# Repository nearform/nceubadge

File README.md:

# NodeConf EU 2017 Badge

### All documentation including the Getting Started Guide and explanations of the sample code in this repo is available on [nodeconfeubadge.org](http://nodeconfeubadge.org)

## Hardware
This is an Open Source Hardware project. Schematics and board design files are available in the /hardware directory

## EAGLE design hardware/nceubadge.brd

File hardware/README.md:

Nodeconf EU hardware design files
=================================

The Badge's hardware was designed in [Eagle CAD](https://www.autodesk.com/products/eagle/overview)

You'll find the original design files here, as well as PDF versions of the schematic and board.

Parts
-----

The main components are:

* [MDBT42Q](http://www.raytac.com/download/MDBT42/MDBT42Q%20&%20MDBT42Q-P-Version%20D.pdf) Bluetooth Module (with [nRF52832](https://www.nordicsemi.com/eng/Products/Bluetooth-low-energy/nRF52832) MCU)
* [MCCOG128064B12W-SPR](http://www.farnell.com/datasheets/2151561.pdf) LCD

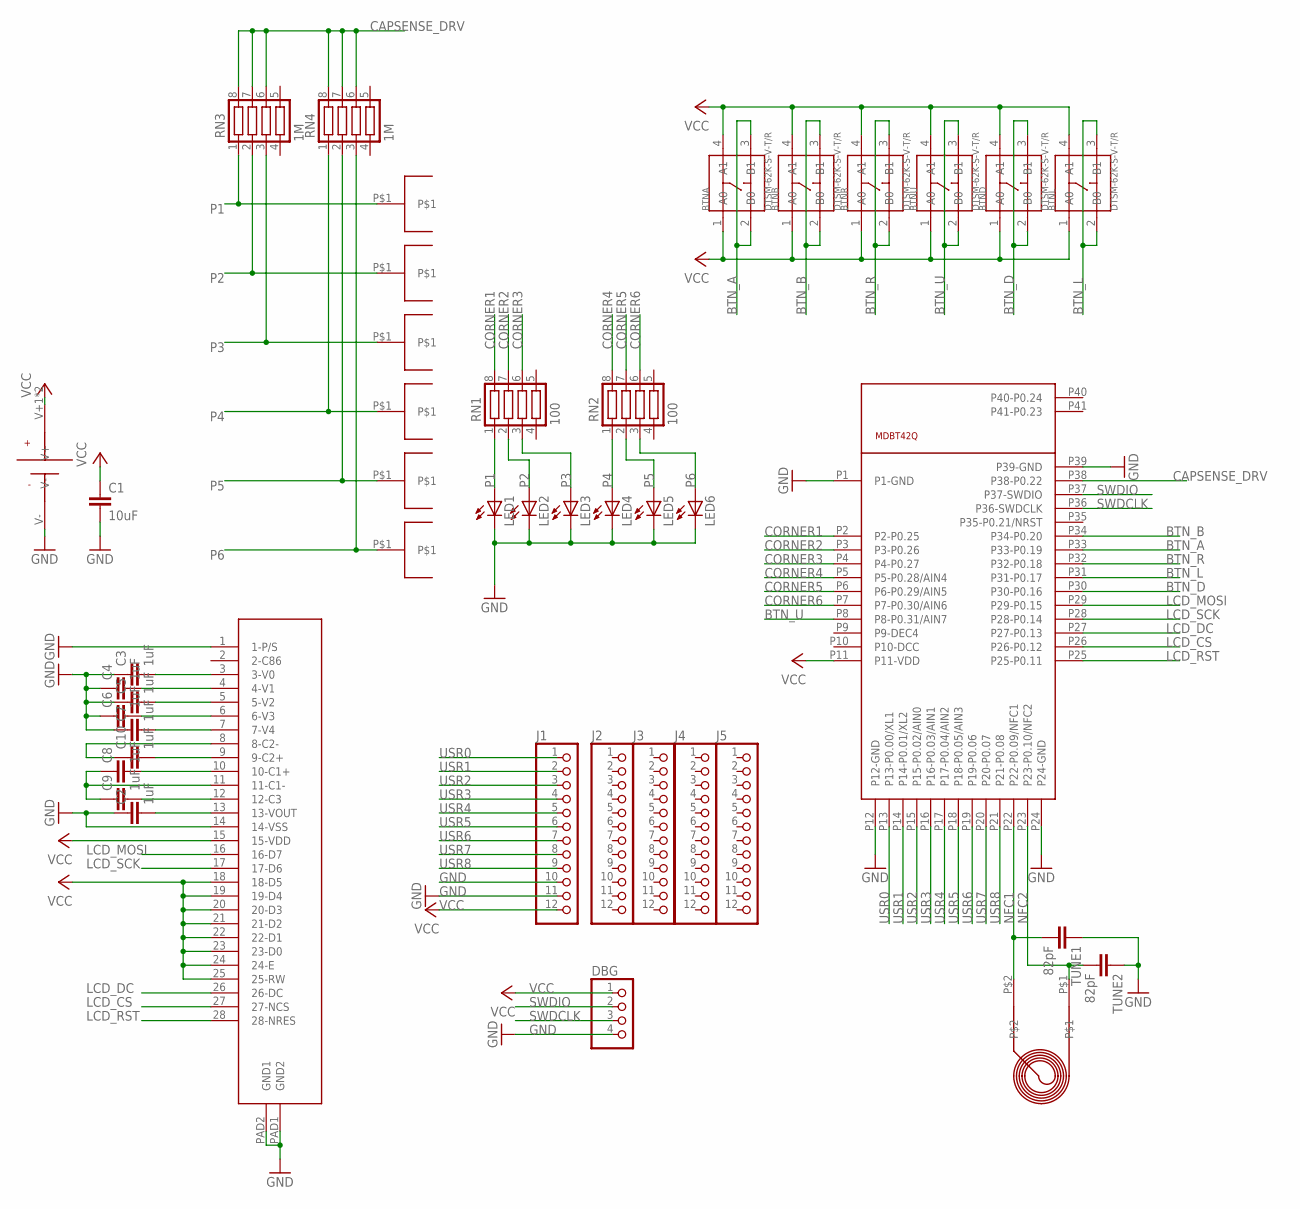
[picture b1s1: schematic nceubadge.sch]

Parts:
BTNA: DTSM-62K-S-V-T/R; SW4-SMD-6.0X6.0X5.0MM
BTNB: DTSM-62K-S-V-T/R; SW4-SMD-6.0X6.0X5.0MM
BTND: DTSM-62K-S-V-T/R; SW4-SMD-6.0X6.0X5.0MM
BTNL: DTSM-62K-S-V-T/R; SW4-SMD-6.0X6.0X5.0MM
BTNR: DTSM-62K-S-V-T/R; SW4-SMD-6.0X6.0X5.0MM
BTNU: DTSM-62K-S-V-T/R; SW4-SMD-6.0X6.0X5.0MM
C1: 10uF; C0805K
C2, C3, C4, C5, C6, C7, C8, C9, C10: 1uF; C0603
DBG: PINHD-1X4; 1X04
J1, J2, J3, J4, J5: PINHD-1X12_2.54-S; 1X12-S
J8: KEYSTONE-3003
LCD: MCCOG128064B12W; MCOG128064B12W-SPR
LED1, LED2, LED3, LED4, LED5, LED6: LED5MM
RN1, RN2: 100; CTS742C083
RN3, RN4: 1M; CTS742C083
TUNE1, TUNE2: 82pF; C0603
U1: MDBT42Q; MDBT40
U$2, U$3, U$4, U$5, U$6, U$7: BANANAPLUG
U$8: NFC

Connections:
BTN_A: BTNA.2 (B0), BTNA.3 (B1), U1.P33 (P33-P0.19)
BTN_B: BTNB.2 (B0), BTNB.3 (B1), U1.P34 (P34-P0.20)
BTN_D: BTND.2 (B0), BTND.3 (B1), U1.P30 (P30-P0.16)
BTN_L: BTNL.2 (B0), BTNL.3 (B1), U1.P31 (P31-P0.17)
BTN_R: BTNR.2 (B0), BTNR.3 (B1), U1.P32 (P32-P0.18)
BTN_U: BTNU.2 (B0), BTNU.3 (B1), U1.P8 (P8-P0.31/AIN7)
CAPSENSE_DRV: RN3.6, RN3.7, RN3.8, RN4.6, RN4.7, RN4.8, U1.P38 (P38-P0.22)
CORNER1: RN1.8, U1.P2 (P2-P0.25)
CORNER2: RN1.7, U1.P3 (P3-P0.26)
CORNER3: RN1.6, U1.P4 (P4-P0.27)
CORNER4: RN2.8, U1.P5 (P5-P0.28/AIN4)
CORNER5: RN2.7, U1.P6 (P6-P0.29/AIN5)
CORNER6: RN2.6, U1.P7 (P7-P0.30/AIN6)
GND: C1.2, C2.1, C3.1, C4.1, C5.1, C6.1, C7.1, DBG.4, J1.10, J1.11, J8.V-, LCD.1 (1-P/S), LCD.14 (14-VSS), LCD.PAD1 (GND2), LCD.PAD2 (GND1), LED1.K (C), LED2.K (C), LED3.K (C), LED4.K (C), LED5.K (C), LED6.K (C), TUNE1.1, TUNE2.1, U1.P1 (P1-GND), U1.P12 (P12-GND), U1.P24 (P24-GND), U1.P39 (P39-GND)
LCD_CS: LCD.27 (27-NCS), U1.P26 (P26-P0.12)
LCD_DC: LCD.26 (26-DC), U1.P27 (P27-P0.13)
LCD_MOSI: LCD.16 (16-D7), U1.P29 (P29-P0.15)
LCD_RST: LCD.28 (28-NRES), U1.P25 (P25-P0.11)
LCD_SCK: LCD.17 (17-D6), U1.P28 (P28-P0.14)
unnamed: C8.1, C9.1, LCD.11 (11-C1-)
unnamed: C8.2, LCD.10 (10-C1+)
unnamed: C9.2, LCD.12 (12-C3)
unnamed: C2.2, LCD.13 (13-VOUT)
unnamed: C7.2, LCD.7 (7-V4)
unnamed: C6.2, LCD.6 (6-V3)
unnamed: C5.2, LCD.5 (5-V2)
unnamed: C4.2, LCD.4 (4-V1)
unnamed: C3.2, LCD.3 (3-V0)
unnamed: C10.2, LCD.9 (9-C2+)
unnamed: C10.1, LCD.8 (8-C2-)
NFC1: TUNE1.2, U1.P22 (P22-P0.09/NFC1), U$8.P$2
NFC2: TUNE2.2, U1.P23 (P23-P0.10/NFC2), U$8.P$1
P1: LED1.A, RN1.1, RN3.1, U$6.P$1
P2: LED2.A, RN1.2, RN3.2, U$7.P$1
P3: LED3.A, RN1.3, RN3.3, U$5.P$1
P4: LED4.A, RN2.1, RN4.1, U$4.P$1
P5: LED5.A, RN2.2, RN4.2, U$3.P$1
P6: LED6.A, RN2.3, RN4.3, U$2.P$1
SWDCLK: DBG.3, U1.P36 (P36-SWDCLK)
SWDIO: DBG.2, U1.P37 (P37-SWDIO)
USR0: J1.1, U1.P13 (P13-P0.00/XL1)
USR1: J1.2, U1.P14 (P14-P0.01/XL2)
USR2: J1.3, U1.P15 (P15-P0.02/AIN0)
USR3: J1.4, U1.P16 (P16-P0.03/AIN1)
USR4: J1.5, U1.P17 (P17-P0.04/AIN2)
USR5: J1.6, U1.P18 (P18-P0.05/AIN3)
USR6: J1.7, U1.P19 (P19-P0.06)
USR7: J1.8, U1.P20 (P20-P0.07)
USR8: J1.9, U1.P21 (P21-P0.08)
VCC: BTNA.1 (A0), BTNA.4 (A1), BTNB.1 (A0), BTNB.4 (A1), BTND.1 (A0), BTND.4 (A1), BTNL.1 (A0), BTNL.4 (A1), BTNR.1 (A0), BTNR.4 (A1), BTNU.1 (A0), BTNU.4 (A1), C1.1, DBG.1, J1.12, J8.V+1 (V+), J8.V+2 (V+), LCD.15 (15-VDD), LCD.18 (18-D5), LCD.19 (19-D4), LCD.20 (20-D3), LCD.21 (21-D2), LCD.22 (22-D1), LCD.23 (23-D0), LCD.24 (24-E), LCD.25 (25-RW), U1.P11 (P11-VDD)

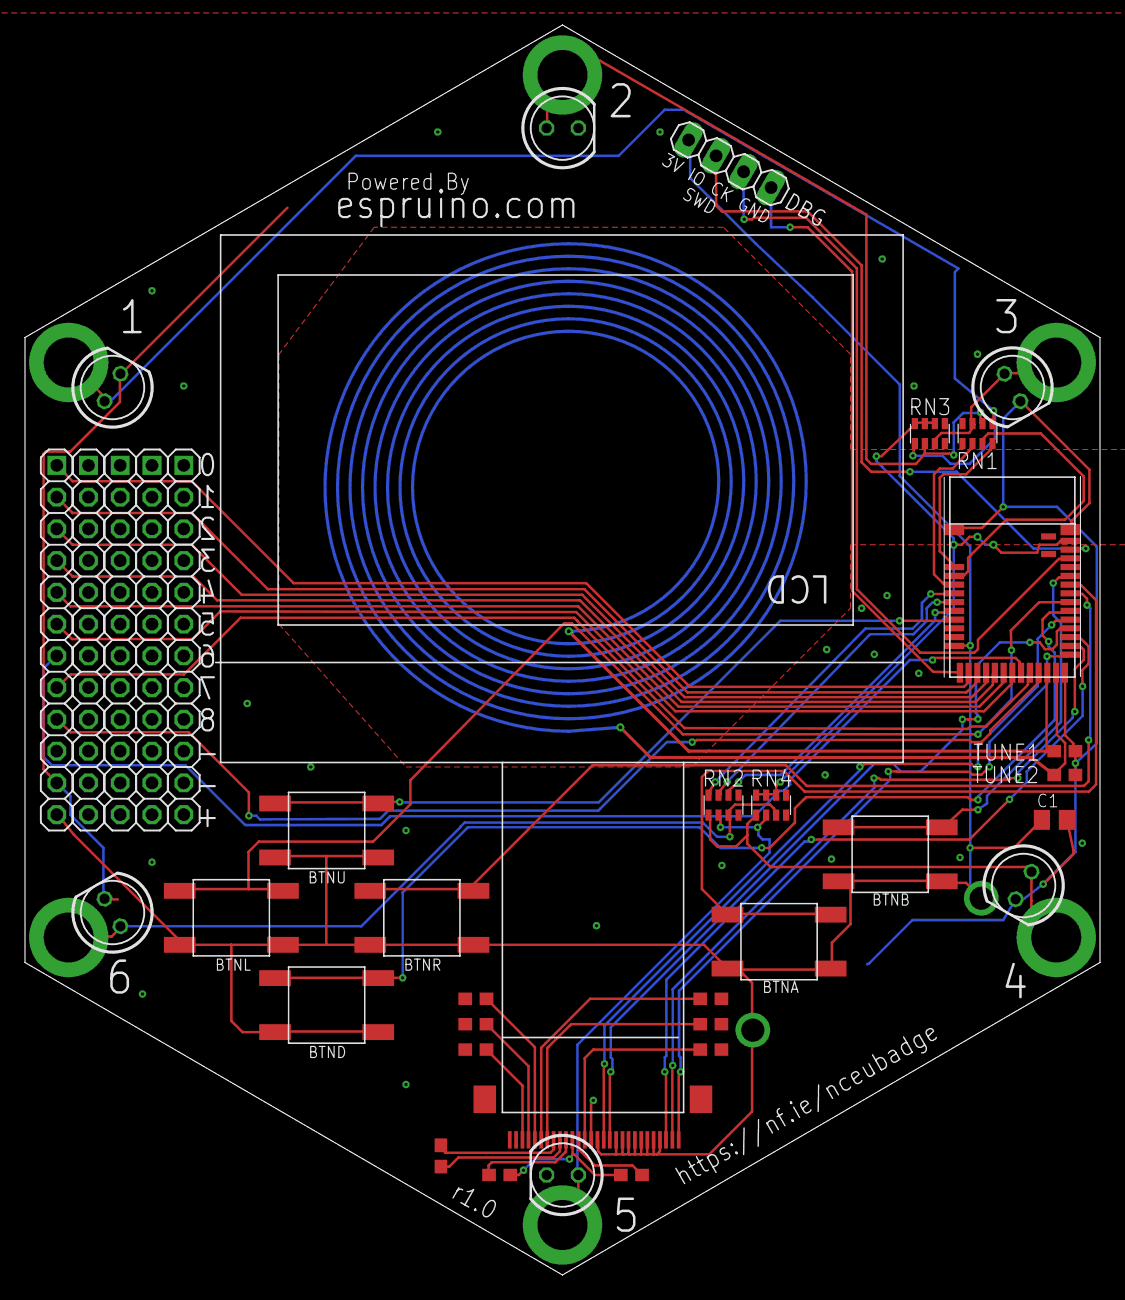
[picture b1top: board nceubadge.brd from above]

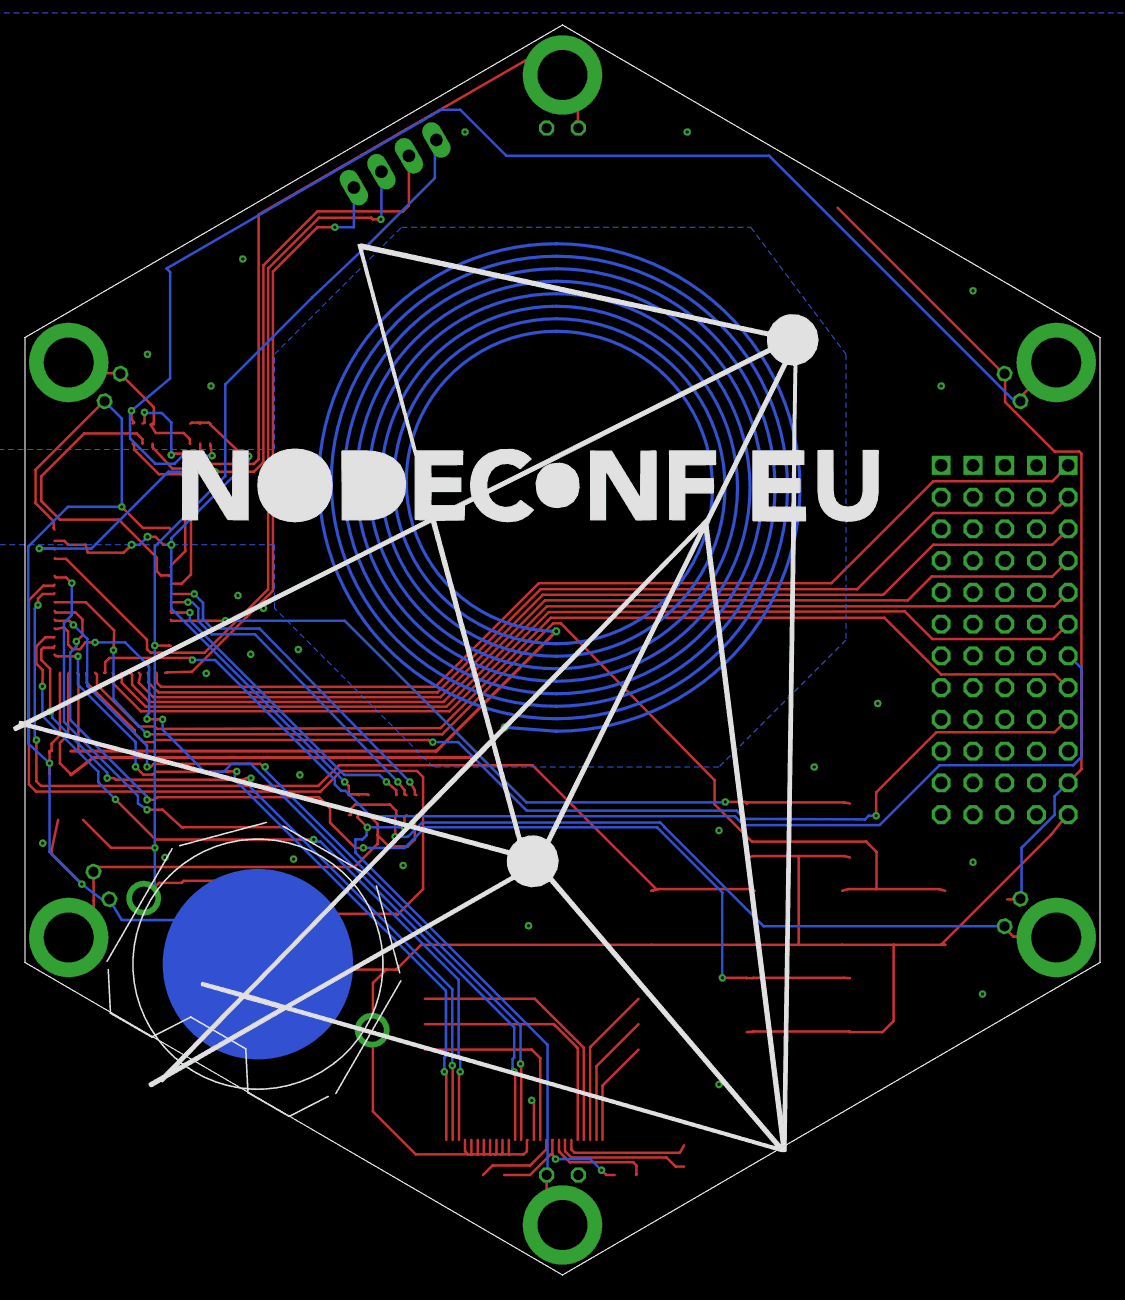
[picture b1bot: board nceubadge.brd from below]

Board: 2 copper layers, 86.0 x 100.0 mm, 44 parts (2 on the bottom side), 50 nets.

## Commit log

2017-08-23 flappy bird
2017-08-23 snake
2017-08-23 minor tweaks
2017-08-23 Click speed counter
2017-08-23 menu example
2017-08-23 Add JS REPL
2017-09-08 new games
2017-10-10 trex
2017-10-10 First hack at main badge code
2017-10-11 use A to jump as well
2017-10-12 badge now cycles through images, and tweaked firmware to allow bigger saved code area so we could add flappy bird
2017-10-12 better konami code
2017-10-12 Add sketch - had to remove some comments so we can get it all in 20k without minifying
2017-10-12 sketch
2017-10-12 oops
2017-10-23 Generate image data from Name input at registration
2017-10-23 improved instructions
2017-10-23 README
2017-10-23 docs
2017-10-23 hardware
2017-10-23 improved font ;-) and centered text
2017-10-24 prepping for dedicated docs site
2017-10-24 improved .gitignore
2017-10-24 images
2017-10-24 basic outline of a docs site
2017-10-24 robots.txt just in case
2017-10-24 robots.txt just in case again
2017-10-24 simple docs building script
2017-10-24 Added outstanding To-Dos and user flow to repo README
2017-10-24 Improved text layout of name on badge. Needs further testing
2017-10-25 added firmware
2017-10-25 tweak
2017-10-25 add flash script
2017-10-25 New text layout tested on multiple names. Seems fine. Switched to Verdana too
2017-10-25 replaced the Fonz with just Hello in case it causes any issues.
2017-10-27 Improved NodeConf EU 2017 logo from Agata
2017-10-28 added main getting started pages (no content) and list of challenges
2017-10-28 all challenge pages created with simple text. Lots of content needed next
2017-10-28 basic display image code
2017-10-28 Simplified board image with some comments explaining how to connect things
2017-10-30 tools to add new images/retrieve existing images from the badge
2017-10-30 Bulk generator of name images and NFC URLs to run in advance of event.
2017-10-30 improved sample data
2017-10-30 make sure real data never committed
2017-10-30 name-generator.js now asks for URL too and then generates single row CSV file to be compatible with bulk generator
2017-10-30 removed more temp files
2017-10-30 more basic setup instructions
2017-10-31 added name in text to CSV outputs
2017-10-31 add scripts for flashing from a CSV file, move main.js and tweak it to allow uploads again
2017-10-31 center text, fix some regressions
2017-10-31 lots of small docs updates. Moved all code info to docs from README to have in one place
2017-11-01 add hacky tool for writing main.js via BLE
2017-11-01 Mention NFC issue. Fix list of built-in apps in docs
2017-11-01 learns how to spell capacitive
2017-11-01 updated firmware
2017-11-01 all challenges now updated except for sound recording which isn't working for me
2017-11-01 a few more doc tweaks
2017-11-01 change judging time
2017-11-02 removed sound recording challenge. Added more info about pin capabilities. May need more info there
2017-11-02 format error fix
2017-11-02 badge now reloads menu after stopping being connectable - adds contents of 'Badge.apps' to the badge menu
2017-11-02 don't pretokenise - we don't need it as running from flash, and it messes up debugging
2017-11-02 predefine apps variable
2017-11-02 Probably Conors last set of direct edits to the docs. From now on we should all PR.
2017-11-02 tiny text and footer tweaks
2017-11-02 extra menu code from Gordon
2017-11-02 extra Web Bluetooth challenge code from Gordon
2017-11-02 placeholder for Gordon's workshop
2017-11-03 first pass at workshop
2017-11-03 add images
2017-11-03 built workshop
2017-11-03 de-duplicate titles
2017-11-03 added more info after the workshop
2017-11-04 quick checkpoint rebuild of docs site
2017-11-05 single name flasher
2017-11-05 tweaks
2017-11-06 make web bluetooth examples executable as-is
2017-11-06 oops #2
2017-11-06 oops #3
2017-11-06 added image upload
2017-11-06 add PartyParrot.js
2017-11-06 Fix link to pre-installed badge code
2017-11-06 a parrot that moves faster the more parrots there are around you!
2017-11-06 fix issue
2017-11-06 defensive check
2017-11-06 fix index ref
2017-11-07 add faq
2017-11-07 update site
2017-11-07 Adding the code to add the Unicorn and unicorn hashtag images to nodeconf badges
2017-11-07 once more with feeling. And content
2017-11-07 spelling error corrected
2017-11-07 was missing a closing brace
2017-11-07 errors were found in user testing. These have been rectified. Now the code both works and displays as expected.
2017-11-07 adding my details
2017-11-07 fixing the URL so it NFC's in the right way
2017-11-07 re-run hugo
2017-11-07 fix date -> add faq
2017-11-08 add a menu option for running proximity parrot and remove the repl
2017-11-08 add LED flashing
2017-11-08 start of CircleCI building
2017-11-08 new Circle location
2017-11-08 new Circle filename
2017-11-23 fix CircleCI config in prep for move to S3/CF and https
2017-11-23 fixed web bluetooth examples. Site now built in CircleCI, hosted on S3/CF and served with https
2018-09-26 stupidly had robobots.txt blocking everything all year
2018-10-19 Quick hack to move to 2018. Needs more content
2018-11-03 added Gordon's notes as a Getting Started Guide
2018-11-04 Getting Started update
2018-11-05 URL tweaks
2018-11-05 typo
2018-11-05 tweak bugs list
2018-11-06 app docs
2018-11-06 espruino updates
2018-11-06 pitfalls
2018-11-07 docs on using CLI
2018-11-11 updated method to change name on Badge
